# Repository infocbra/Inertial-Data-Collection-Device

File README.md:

>  printed circuit board and code for collecting inertial data to research purposes of movements.

## About
Hardware developed to collect inertial data of humans (i.e. Accelerometer, Giroscope) and temperature in order to provide an open source hardware for researchs related to the analysis of human movements for many purposes.<br>
This project was tested in the diagnosis and prognosis of neuromotor diseases - Parkinson's disease mostly as part of the project of scientific research [**"Visualization Strategies to Online Big Data applied in individualized medicine"**](https://github.com/Wanghley/PIBIC-Strategies-Data-Visualization-Medicine).

## Requirements
| Dependency | Platform | Description |
| :--------- | -------- | :---------- |
| [arduino_2012](https://github.com/Wanghley/Inertial-Data-Collection-Device/blob/main/lib/arduino_2012.lbr) | eagle lib | arduino schematic and layout to **Eagle** project |
| [con-headers-jp](https://github.com/Wanghley/Inertial-Data-Collection-Device/blob/main/lib/con-headers-jp.lbr) | eagle lib | schematic and layout of female pin bars to **Eagle** project |
| [DIY modules](https://github.com/Wanghley/Inertial-Data-Collection-Device/blob/main/lib/diy-modules.lbr) | eagle lib | bluetooth adaptor fotoprint and symbol to **Eagle** project |
| [KRE](https://github.com/Wanghley/Inertial-Data-Collection-Device/blob/main/lib/kre.lbr) | eagle lib | borne connector fotoprint and symbol to **Eagle** project |
| [pinhead](https://github.com/Wanghley/Inertial-Data-Collection-Device/blob/main/lib/pinhead.lbr) | eagle lib | added in the **Eagle** project for auxiliary view of pin bars |
| [TimerOne 1.1.0](https://github.com/Wanghley/Inertial-Data-Collection-Device/blob/main/lib/TimerOne-1.1.0.zip) | arduino lib | allow running a periodic interrupt function based in finer PWM control |
| [MPU6050 0.2.1](https://github.com/Wanghley/Inertial-Data-Collection-Device/blob/main/lib/MPU6050-0.2.1.zip) | arduino lib | allow MPU6050 easy control and manipulation |
| [Wire](https://www.arduino.cc/en/reference/wire) | arduino lib | allow communication over I2C protocol |
| [SoftwareSerial](https://www.arduino.cc/en/Reference/softwareSerial) | arduino lib | allow serial communication on other digital pins of the Arduino |

## Bill of Materials
| # | Designator | Qty | Description | Obs |
| - | :--------- | --- | :---------- | :---------- | 
| 1 | R1, R2 | 2 | Resistor 220R 5% (1/4W) | Used for digital protection of bluetooth module RX |
| 2 | HC-05 | 1 | HC-05 Bluetooth Module | Module of Low supply consumption for prototype communication |
| 3 | PUSH | 2 | Push Button Long Head | Push button for hardware control and operation  |
| 4 | ON/OFF | 1 | 255sb sliding switch | Sliding switch to control energy supply of the prototype |
| 5 | LED1 | 1 | COM-09590 | 2.25 V Red LED 5mm Cylindrical indicates the hardware is ready for collection |
| 6 | LED2 | 1 | COM-09590 | 2.25 V green LED 5mm Cylindrical indicates the hardware operation mode and collection in process |
| 6 | Arduino Nano | Arduino Nano | | mother board and controller |
| 7 | KRE-2P | 1 | Borne Connector | Connector to the batery |
| 8 | BATTERY CHARGER | 1 | TP4056 | Power supply adn voltage regulator to the batery |
| 9 | RGB_LED | 1 | LED RBG 5MM | RGB LED 5mm Cylindrical indicates the mode of operation of the device |

## Development
In order to run and contribute to the PCB development you must have **Eagle**  installed in your computer and then use the .sch to work on the circuit itself and the .brd to work in the layout design.

Now, for the development under de code of hardware control you must have Arduino IDE or similar to work on the .ino code.

## Authors
*   **Wanghley Soares Martins** - *junior researcher* - [wanghley](https://github.com/wanghley)
*   **Fábio Henrique Monteiro Oliveira** - *research advisor* - [oliveirafhm](https://github.com/oliveirafhm)

See also the list of [contributors](https://github.com/Wanghley/PIBIC-Strategies-Data-Visualization-Medicine/contributors) who participated in this project.

## License
This project is licensed under the MIT License - see the [LICENSE.md](LICENSE.md) file for details

## Acknowledge
*   Remember, the project is free for you to use, manipulate, change and distribute. However, I am just asking you to mention us in any copy, modification as the root of your development.
*   I would advice you to try out the hardware with an analysis of the result data.
*   If you want an easier software for hardware control, check out the [CONTROL SOFTWARE](https://github.com/Wanghley/PIBIC-Strategies-Data-Visualization-Medicine)
### JOBS TODO
- [x] Update manufacturing images
- [x] Update 3D assembled prototype
- [x] Update gerber file
- [x] Update header
- [ ] Update descripiting photo
- [ ] Make use fluxogram
- [x] Update list of components
- [ ] Make list of buy components

## Gallery
General view of the projected PCB. For more images go to [images/](https://github.com/Wanghley/Inertial-Data-Collection-Device/tree/main/images) and if you still want to see more you can see 3D views on [view/](https://github.com/Wanghley/Inertial-Data-Collection-Device/tree/main/view)

|  | |
|-|-|

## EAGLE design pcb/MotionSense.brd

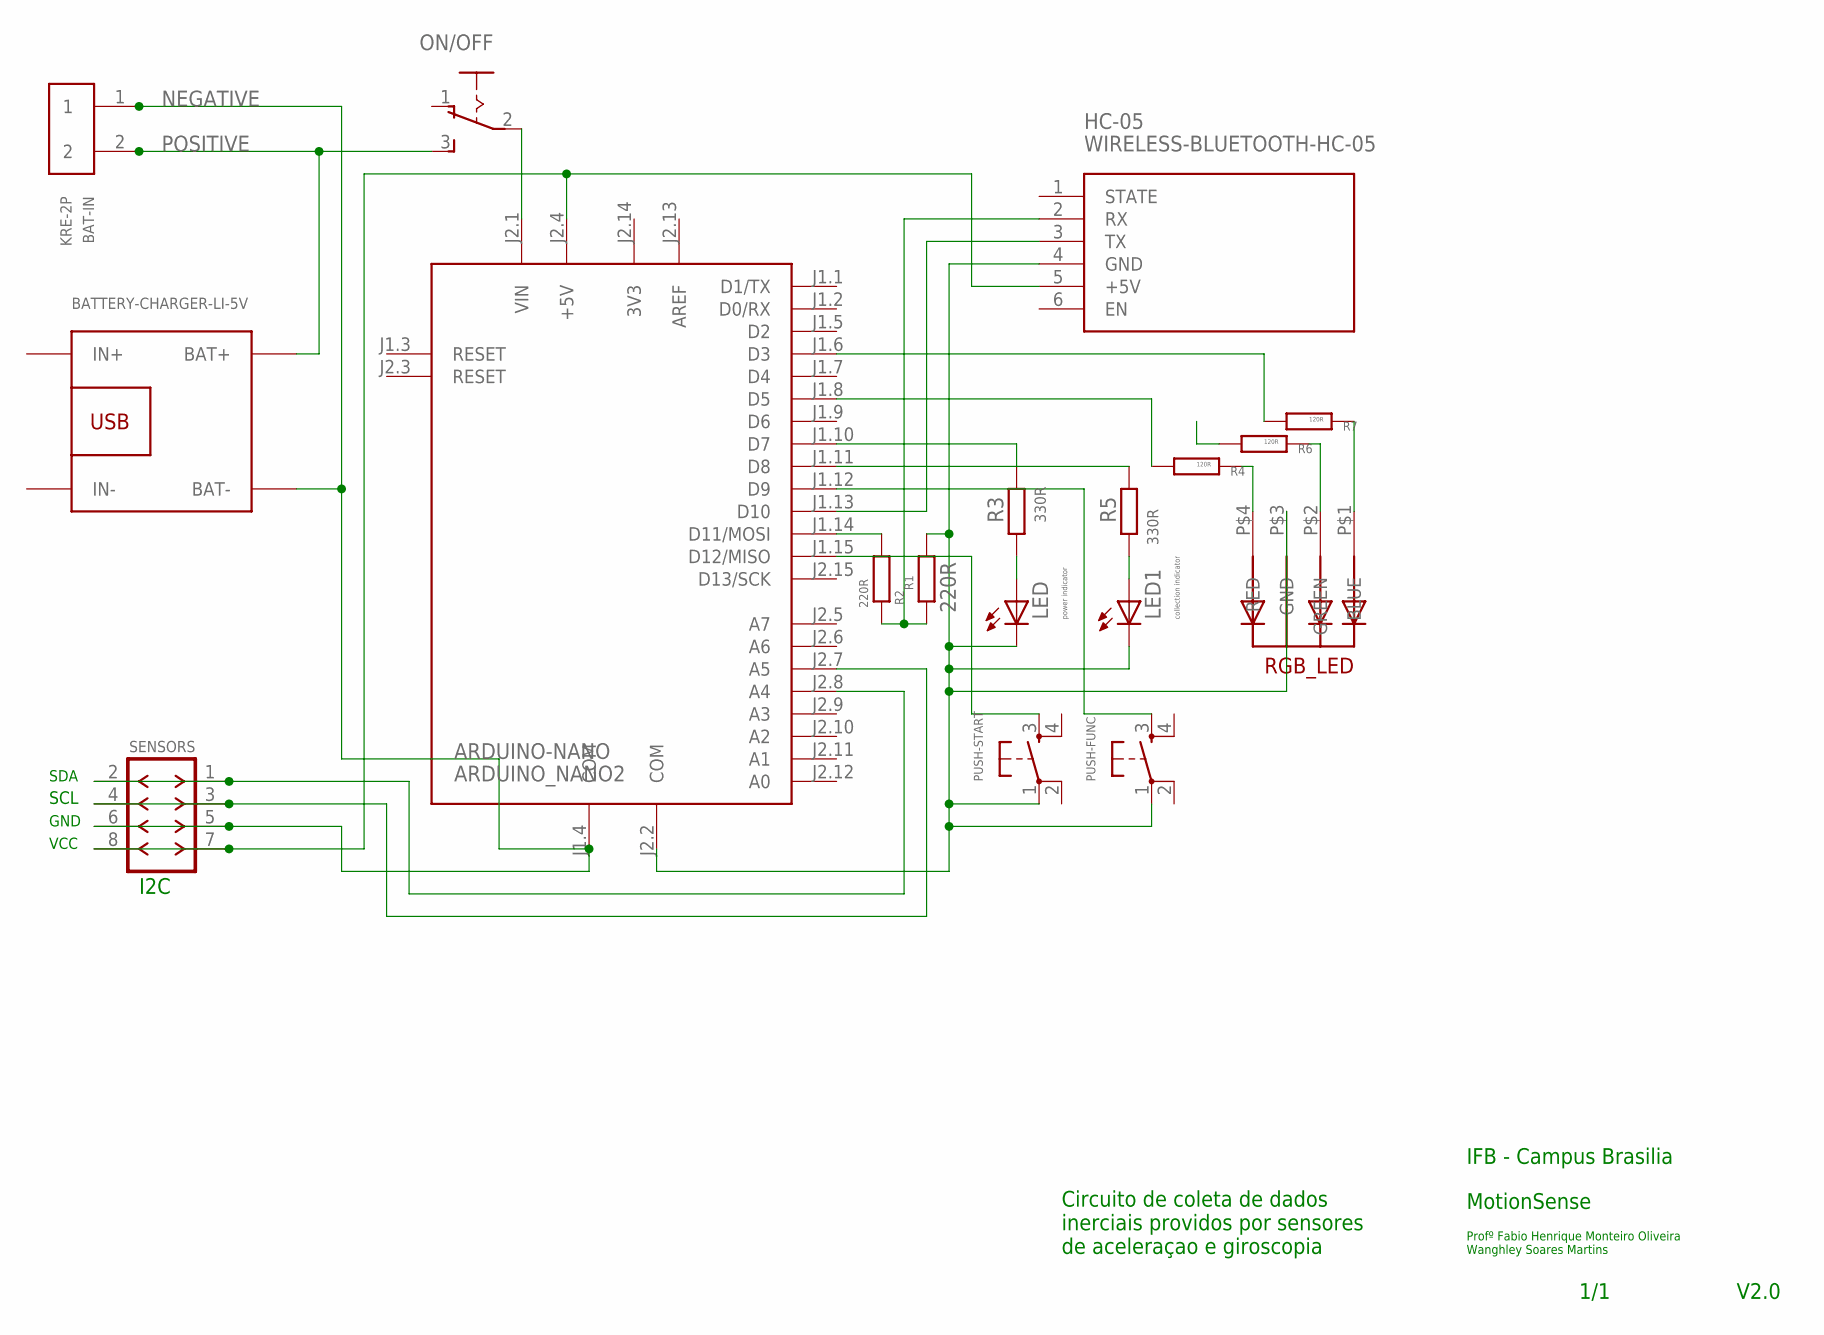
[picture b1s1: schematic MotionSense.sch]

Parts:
ARDUINO-NANO: ARDUINO_NANO2
BAT-IN: KRE-2P
HC-05: WIRELESS-BLUETOOTH-HC-05
LED: power indicator; LED5MM
LED1: collection indicator; LED5MM
ON/OFF: 255SB
PUSH-FUNC: DTS-6
PUSH-START: DTS-6
R1, R2: 220R; 0207/10
R3, R5: 330R; 0207/10
R4, R6, R7: 120R; 0204/7
RGB_LED: 5MMRGBLED; LED5MMRGB
SENSORS: F-2X04-DIL-2MM_M; DIL-2MM-2X04_M
U$1: BATTERY-CHARGER-LI-5V

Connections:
3V3: ARDUINO-NANO.J2.14 (3V3)
AREF: ARDUINO-NANO.J2.13 (AREF)
unnamed: LED.A, R3.1
unnamed: ARDUINO-NANO.J2.4 (+5V), HC-05.5 (+5V), SENSORS.7, SENSORS.8
unnamed: ARDUINO-NANO.J1.14 (D11/MOSI), R2.1
unnamed: ARDUINO-NANO.J2.2 (COM), HC-05.4 (GND), LED.K (C), LED1.K (C), PUSH-FUNC.1, PUSH-START.1, R1.2, RGB_LED.P$3 (GND)
unnamed: ARDUINO-NANO.J1.13 (D10), HC-05.3 (TX)
unnamed: HC-05.2 (RX), R1.1, R2.2
unnamed: ARDUINO-NANO.J2.7 (A5), SENSORS.3, SENSORS.4
unnamed: ARDUINO-NANO.J2.8 (A4), SENSORS.1, SENSORS.2
unnamed: ARDUINO-NANO.J1.10 (D7), R3.2
unnamed: ARDUINO-NANO.J1.15 (D12/MISO), PUSH-START.3
unnamed: ARDUINO-NANO.J2.1 (VIN), ON/OFF.2
unnamed: ARDUINO-NANO.J1.12 (D9), PUSH-FUNC.3
unnamed: ARDUINO-NANO.J1.11 (D8), R5.2
unnamed: LED1.A, R5.1
unnamed: R4.2, RGB_LED.P$4 (RED)
unnamed: R6.2, RGB_LED.P$2 (GREEN)
unnamed: R7.2, RGB_LED.P$1 (BLUE)
unnamed: ARDUINO-NANO.J1.8 (D5), R4.1
unnamed: ARDUINO-NANO.J1.6 (D3), R7.1
NEGATIVE: ARDUINO-NANO.J1.4 (COM), BAT-IN.1, SENSORS.5, SENSORS.6, U$1.BAT-
POSITIVE: BAT-IN.2, ON/OFF.3 (S), U$1.BAT+

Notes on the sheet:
Circuito de coleta de dados inerciais providos por sensores de aceleraçao e giroscopia
MotionSense
IFB - Campus Brasilia
Profº Fabio Henrique Monteiro Oliveira Wanghley Soares Martins
V2.0
1/1
I2C
VCC
GND
SCL
SDA

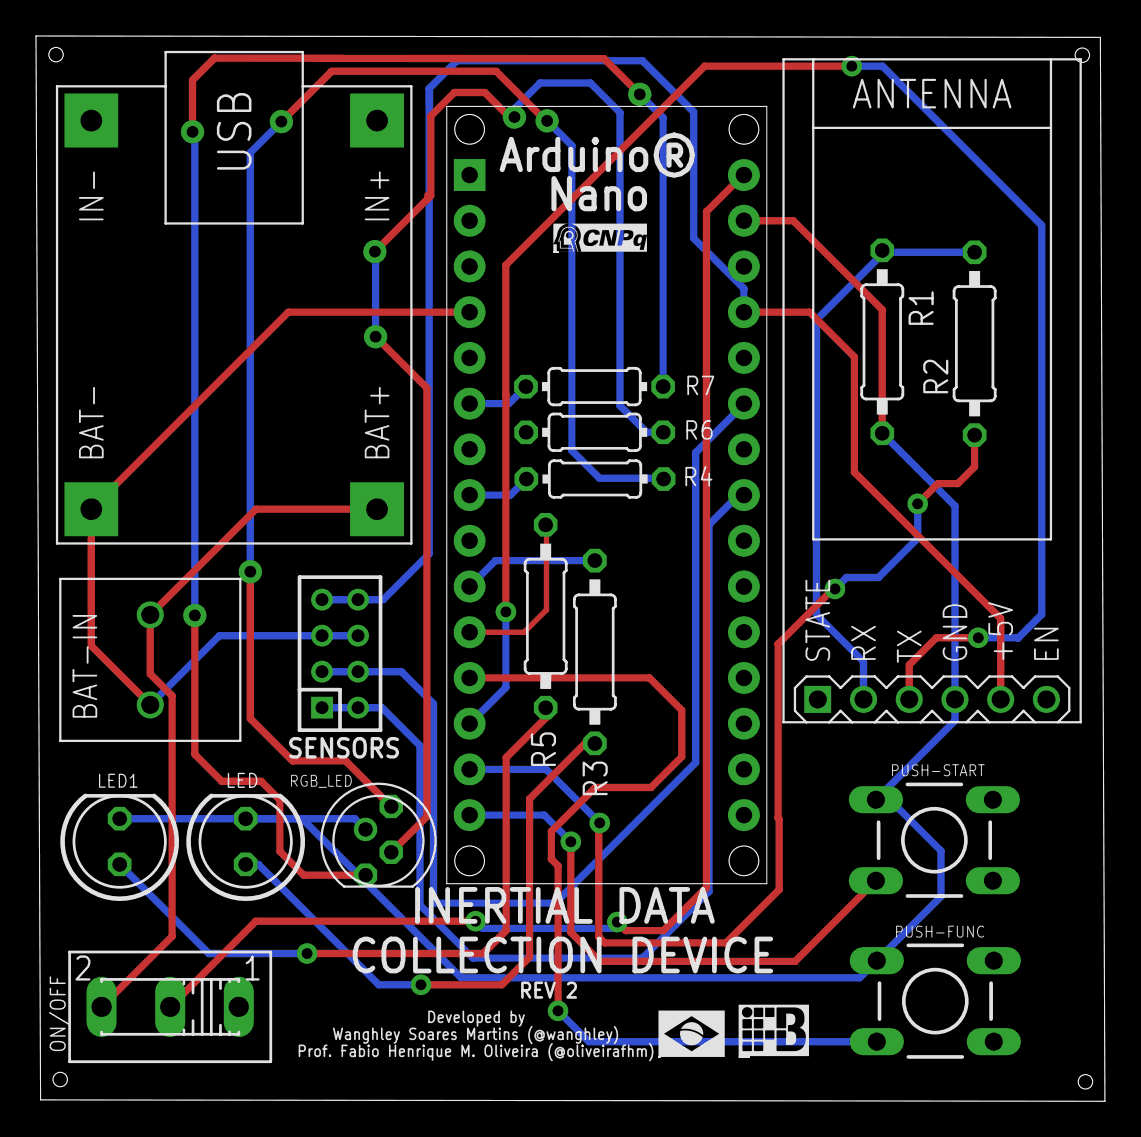
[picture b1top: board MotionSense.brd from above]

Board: 2 copper layers, 59.4 x 59.2 mm, 18 parts (0 on the bottom side), 21 nets.

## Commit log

2020-11-19 [UPDATE] adding README mainly content and structure
2020-11-19 [UPDATE]correciton of repository's title
2020-11-29 [ADD] images prototype version 1.0
2020-11-29 [ADD] version 1 prototype finished
2020-11-29 [UPDATE] bug correction and library problems
    2 leds
    2 push btns
    refactor sensors I2C connector
2020-11-29 [UPDATE]libraries addition to next version of PCB
2020-11-29 [ADD]gitignore & gitattributes
2020-11-30 [ADD]controller code from previous repository
    If you want to see previous versions of the code you must go to PIBIC project to see further infos
2020-11-30 [UPDATE]connection bug fix
2020-11-30 [UPDATE] PCB update v2
2020-11-30 [UPDATE]view settings
2020-11-30 [UPDATE]adding dimension measurement
    The measurement is in mm
2020-11-30 [REMOVE]unnecessary file
2020-11-30 [UPDATE] drilling addition
2020-11-30 [ADD]board manufacturing picture REV2 addition
2020-11-30 [UPDATE] connection missing bug fixing
    connection to the ground was not done.
2020-11-30 [ADD]cam outputs for gerber files generation
2020-11-30 [ADD]pcb 3D visualization file
2020-11-30 [ADD]PCB with assembled parts to preview
    3D visualization of the real prototype of Inertial Data Collection Device
2020-11-30 [UPDATE]stl High and standard quality addition
2020-11-30 [ADD]glb pcb+assemblies view
2020-11-30 [ADD] bitmap board assembled
2020-11-30 [ADD] cover to README file
2020-11-30 [UPDATE] add cover to readme file
2020-11-30 [UPDATE] authors name addition
2020-11-30 [UPDATE]removing wrong white background
2020-11-30 [ADD]cover GIMP project
2020-11-30 [UPDATE]removing unnecessary topics
2020-11-30 [UPDATE] identation fixing
2020-11-30 [UPDATE]identation fixing
2020-11-30 [UPDATE]unitialized variable correction
2020-11-30 [UPDATE]variable asssigned but value never used correction
2020-11-30 [UPDATE]buffer boundaries used correction try
2020-11-30 [UPDATE]reversing last commit
2020-11-30 [ADD]MPU6050 library
2020-11-30 [ADD]TimerOne library
2020-11-30 [UPDATE]requirements addition
2020-11-30 [UPDATE]bill materials addition
2020-11-30 [UPDATE] readme development instructions
2020-11-30 [UPDATE]release badge addition
2020-11-30 [UPDATE]acknowledge addition
2020-11-30 [UPDATE]incorrect indent on acknowledge fixing
2020-11-30 [ADD]prototype rev1 SQ 3D view
2020-11-30 [ADD]prototype rev1 HQ 3D view
2020-11-30 [UPDATE]refactoring name to revs
2020-11-30 [UPDATE]refactoring name to rev2
2020-11-30 [ADD]rev1 3D view
2020-11-30 [UPDATE]refactoring name to rev1
2020-11-30 [ADD]diagram of components
2020-11-30 [UPDATE]README gallery addition
2020-12-01 [UPDATE] README
2020-12-02 [UPDATE]gallery view correction
2020-12-03 [UPDATE]no consecutive blank line
2020-12-03 [UPDATE]pads correction to up to 1.4mm
2020-12-03 [ADD]eagle CAM config
2020-12-03 [ADD]gerber file
2020-12-03 [UPDATE]gbr file update
2020-12-03 [UPDATE]gerber pads correction
2020-12-06 [UPDATE]RGB LED addition to project
    RGB led to indicates the mode of operation of the device
2020-12-06 [UPDATE]projeting led RGB pcb connection and positionating
2020-12-06 [UPDATE]Gerber file with RGB LED
2020-12-06 [UPDATE]cam
2020-12-06 [UPDATE]PCB manufacturing preview update
    update with rgb led added to the project
2020-12-06 [UPDATE] TODO list of the repository
2020-12-06 [UPDATE]image cutting and resizing
2020-12-06 [UPDATE]manufacturing gallery position
2020-12-06 [UPDATE]TODO list addition
2020-12-10 [UPDATE]3D view update
2020-12-10 [UPDATE]image motion sense rev2
2020-12-10 [UPDATE]cover
2020-12-10 [UPDATE]3D view of prototype
2020-12-10 [UPDATE]README 3D
2020-12-10 [UPDATE]README
2020-12-17 [UPDATE]bug drills fixing
2020-12-17 [ADD]PCB pdf view
2020-12-17 [ADD]Schematic pdf view
2021-01-05 [UPDATE] correction 90deg angles removing
2021-01-05 [UPDATE] CAM view
2021-01-05 [UPDATE] Gerber File
2021-06-24 [UPDATE] code refactor location and version 2 hardware update
2021-06-24 [UPDATE] operation mode starter work & code optimization
2021-07-15 [UPDATE] three functions control operating finished
2021-07-16 [UPDATE] change RGB ports to right PWM

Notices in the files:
parts and their libraries:
diy-modules: Released under the Creative Commons Attribution 4.0 International License: http://creativecommons.org/licenses/by/4.0
con-headers-jp: Copyright (C) 2008, Bob Starr
